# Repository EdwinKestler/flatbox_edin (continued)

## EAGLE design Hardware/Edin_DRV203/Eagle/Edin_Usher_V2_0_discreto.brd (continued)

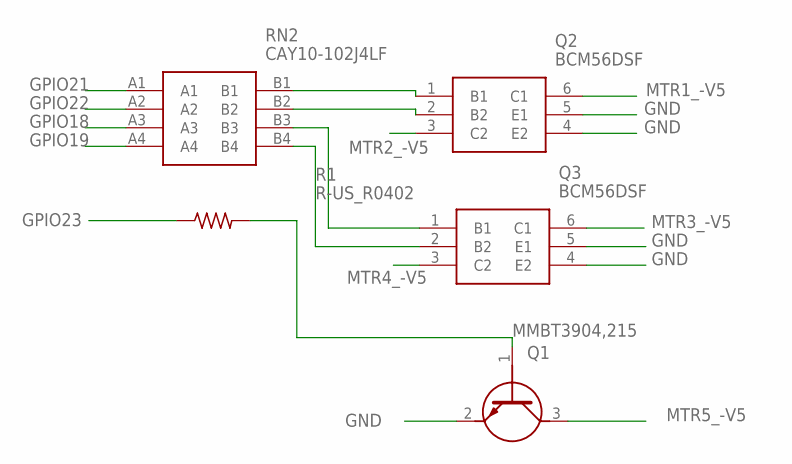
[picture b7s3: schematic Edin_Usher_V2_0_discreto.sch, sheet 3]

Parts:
Q1: MMBT3904,215; SOT95P230X110-3N
Q2, Q3: BCM56DSF; SOT95P275X110-6N
R1: R-US_R0402; R0402
RN2: CAY10-102J4LF; CAY10102J4LF

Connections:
GND: Q1.2 (E), Q2.4 (E2), Q2.5 (E1), Q3.4 (E2), Q3.5 (E1); also elsewhere on the board
GPIO18: RN2.A3; also elsewhere on the board
GPIO19: RN2.A4; also elsewhere on the board
GPIO21: RN2.A1; also elsewhere on the board
GPIO22: RN2.A2; also elsewhere on the board
GPIO23: R1.1; also elsewhere on the board
MTR1_-V5: Q2.6 (C1); also elsewhere on the board
MTR2_-V5: Q2.3 (C2); also elsewhere on the board
MTR3_-V5: Q3.6 (C1); also elsewhere on the board
MTR4_-V5: Q3.3 (C2); also elsewhere on the board
MTR5_-V5: Q1.3 (C); also elsewhere on the board
unnamed: Q1.1 (B), R1.2
unnamed: Q2.1 (B1), RN2.B1
unnamed: Q2.2 (B2), RN2.B2
unnamed: Q3.1 (B1), RN2.B3
unnamed: Q3.2 (B2), RN2.B4

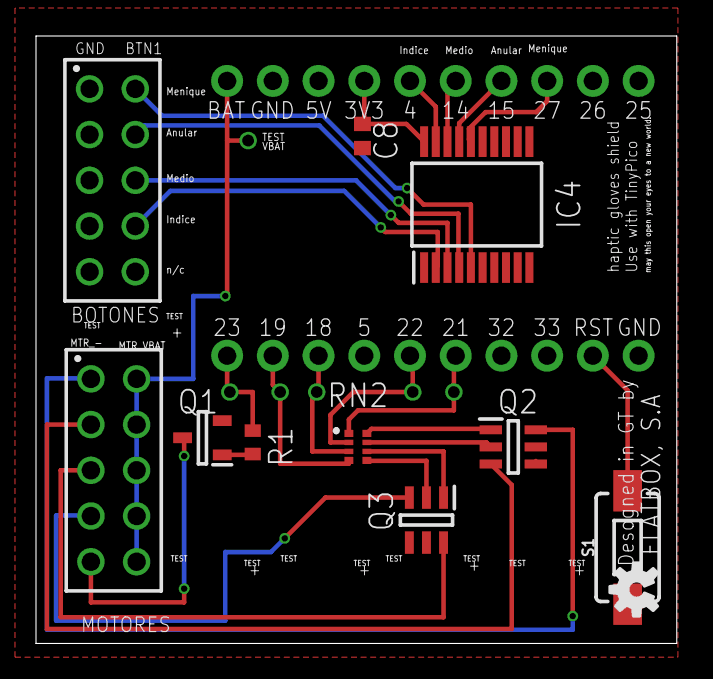
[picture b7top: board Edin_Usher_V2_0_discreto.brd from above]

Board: 2 copper layers, 35.6 x 33.7 mm, 14 parts (1 on the bottom side), 27 nets.

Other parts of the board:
LOGO2: OSHW-LOGOS; OSHW-LOGO-S

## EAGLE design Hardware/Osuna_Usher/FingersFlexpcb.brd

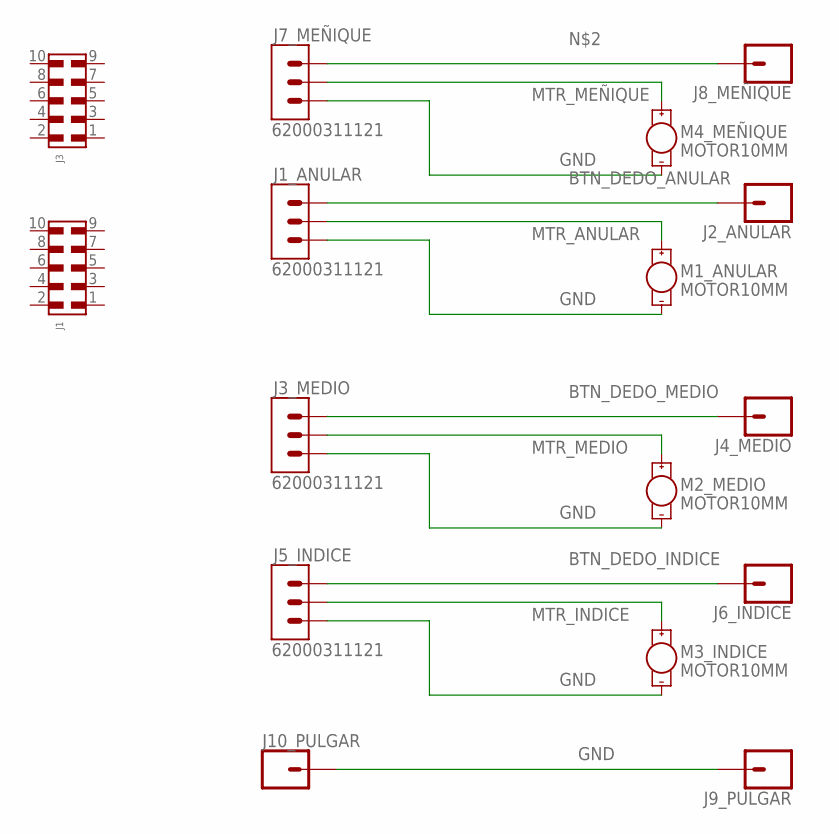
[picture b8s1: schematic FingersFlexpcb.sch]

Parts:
J1, J3: 6100XX21121_61001021121; 61001021121
J1_ANULAR, J3_MEDIO, J5_INDICE, J7_MEÑIQUE: 62000311121
J2_ANULAR, J4_MEDIO, J6_INDICE, J8_MEÑIQUE, J9_PULGAR, J10_PULGAR: CONN_01; 1X01
M1_ANULAR, M2_MEDIO, M3_INDICE, M4_MEÑIQUE: MOTOR10MM; VIBE-MOTOR-10MM

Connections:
BTN_DEDO_ANULAR: J1_ANULAR.1, J2_ANULAR.1
BTN_DEDO_INDICE: J5_INDICE.1, J6_INDICE.1
BTN_DEDO_MEDIO: J3_MEDIO.1, J4_MEDIO.1
GND: J1_ANULAR.3, J3_MEDIO.3, J5_INDICE.3, J7_MEÑIQUE.3, J9_PULGAR.1, J10_PULGAR.1, M1_ANULAR.-, M2_MEDIO.-, M3_INDICE.-, M4_MEÑIQUE.-
MTR_ANULAR: J1_ANULAR.2, M1_ANULAR.+
MTR_INDICE: J5_INDICE.2, M3_INDICE.+
MTR_MEDIO: J3_MEDIO.2, M2_MEDIO.+
MTR_MEÑIQUE: J7_MEÑIQUE.2, M4_MEÑIQUE.+
unnamed: J7_MEÑIQUE.1, J8_MEÑIQUE.1

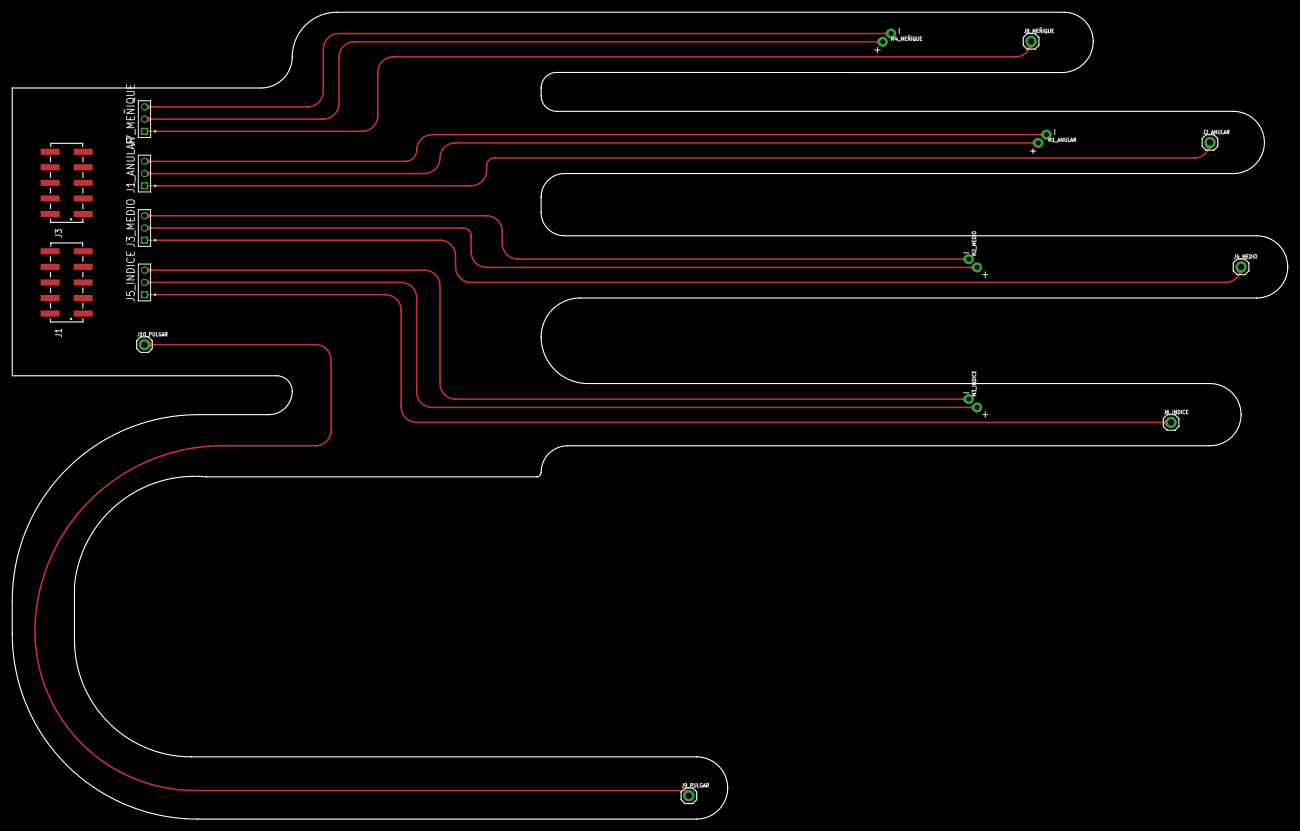
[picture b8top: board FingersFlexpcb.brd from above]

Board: 2 copper layers, 208.3 x 131.8 mm, 16 parts (0 on the bottom side), 9 nets.

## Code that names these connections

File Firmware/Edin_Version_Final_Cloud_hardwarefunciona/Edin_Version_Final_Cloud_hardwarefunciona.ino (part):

/**Attached interrupts
  *GPIO27   --->    SW_PUSH_MENIQUE
  *GPIO15   --->    SW_PUSH_ANULAR
  *GPIO14   --->    SW_PUSH_MEDIO
  *GPIO04   --->    SW_PUSH_INDICE
  ***********
  *PWM MOTORS 
  * GPIO23    --->    MTR_5
  * GPIO19    --->    MTR_4
  * GPIO18    --->    MTR_3
  * GPIO05    --->    MTR_2
  * GPIO32    --->    MTR_1
  * GPIO33    --->    ENABLE
  * 
   */
  
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
//Mapa de asignacion de puertos y canales para PWM ver esquematico para confirmar puertos.

vmotor MTR_5 = {23, 4}; //GPIO23 canal 4
vmotor MTR_4 = {19, 3}; //GPIO19 canal 3
vmotor MTR_3 = {18, 2}; //GPIO18 canal 2
vmotor MTR_2 = {5,  1}; //GPIO5 canal 1
vmotor MTR_1 = {32, 0}; //GPIO32 canal 0

//*******************************************************************************Funcion de PWM para puerto 32 y 33 del ESP32
void aPinMode(int pinNum, int pinDir) {
  // Enable GPIO32 or 33 as output. 
  if (pinNum == 32 || pinNum == 33) {
    uint64_t gpioBitMask = (pinNum == 32) ? 1ULL<<GPIO_NUM_32 : 1ULL<<GPIO_NUM_33;
    gpio_mode_t gpioMode = (pinDir == OUTPUT) ? GPIO_MODE_OUTPUT : GPIO_MODE_INPUT;
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
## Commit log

2020-08-31 pudated REadme
    to initial commit
2020-08-31 ESP32 design files V3
    SMD components
2020-09-01 documents updated
    Not the initial commit any more
2020-09-01 App and aPi Src
    source code for app and API
2020-09-03 STL files for ptrinting
    Printing.
2020-10-16 changed licencing
    Changed Licencing
2020-10-16 Create Hardware LICENSE-CERN-OHL.txt
    Licencing
2020-10-16 Licencice CC-BY-SA
    added Licence CC-BY-SA
2020-10-16 Update LICENSE
2020-10-16 Create CERN LICENCE for Hardware
    HardWare
2020-10-16 added FirmWare
    added FirmWare
2020-10-23 deleted un licensed software
    turns out app software is nor opensource.
2020-10-23 added Sistem configuration
    agregado un diagrama de configracion de sistema.
2020-10-23 Agregado diagrama en PNG
    Diagrama en PNG
2020-10-23 added png to readme
    addes png to readme
2020-12-19 Update to MVP versions
    Update repository to latest development.
2021-01-23 added Cloud tested Firmware version
    Se agrego la version provada del firmware hsata conexxion y recepcionde applicacion en la nube.
2021-08-02 node red POT to APP
    Node red flow to POST to WebAPP
